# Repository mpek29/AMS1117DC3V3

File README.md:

# AMS1117DC3V3

## 🚀 Overview

An open-source reverse-engineered version of the AMS1117 3.3V DC-DC buck converter module, based on the original component available [here](https://fr.aliexpress.com/item/1005006783027108.html).  
This project aims to provide insights into DC-DC voltage regulation and offer a customizable alternative for power management in embedded systems.

## 🎯 Purpose
- 🔍 **Reverse engineering**: Understanding the design and functionality of the AMS1117-based voltage regulator.
- 🛠️ **Skill development**: Enhancing expertise in PCB design and power electronics.
- 🔄 **Future adaptation**: Leveraging this knowledge to develop custom voltage regulation solutions for embedded applications.

## 📝 Features Comparison: Original vs. Reverse-Engineered

| Feature            | Original Module | Reverse-Engineered Version |
|--------------------|----------------|---------------------------|
| 🖥️ PCB Design        | Proprietary     | Open-source & customizable |
| 🔌 Input Voltage    | 4.8V - 15V       | 4.8V - 15V |
| ⚡ Output Voltage   | 3.3V (fixed)     | 3.3V (fixed) |
| 📦 Max Current     | 1500 mA            | 1500 mA |
| 🏷️ Regulator Chip  | AMS1117-3.3      | AMS1117-3.3 |
| 👐 Mechanical Drawing  |  |  |
| 📝 Reverse-Engineered Schematic | N/A |  |
| 📷 Photo             |  |  |

## 🛠️ How to Use
### 📌 Wiring Guide
| Pin  | Description |
|------|-------------|
| VIN  | Input Voltage (4.8V - 15V) |
| GND  | Ground |
| VOUT | Regulated 3.3V Output |

## 🌟 License
This project is open-source. Feel free to use, modify, and contribute! 🚀

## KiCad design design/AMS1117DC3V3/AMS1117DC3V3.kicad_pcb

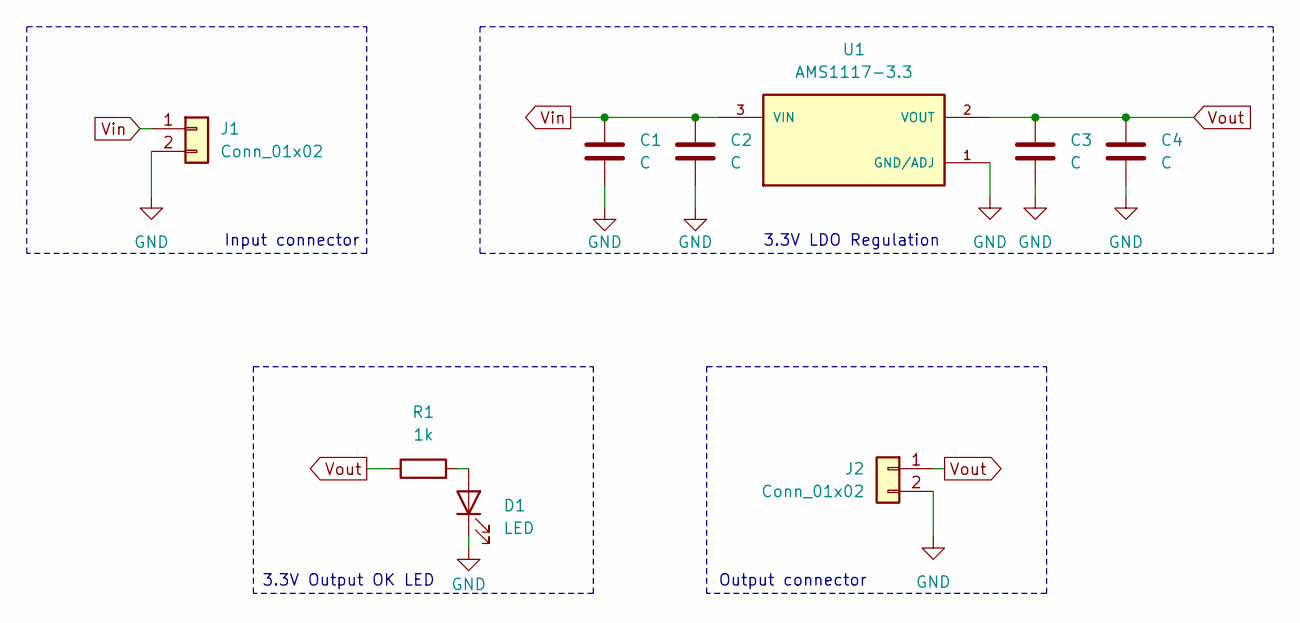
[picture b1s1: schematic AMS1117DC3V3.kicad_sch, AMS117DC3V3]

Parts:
C1, C2, C3, C4: C; C_0603_1608Metric
D1: LED; LED_1206_3216Metric
J1, J2: Conn_01x02; PinHeader_1x02_P2.54mm_Vertical
R1: 1k; R_1206_3216Metric
U1: AMS1117-3.3; SOT229P700X180-4N; PARTREV N/A

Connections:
GND: C1.2, C2.2, C3.2, C4.2, D1.1 (K), J1.2, J2.2, U1.1 (GND/ADJ)
unnamed: D1.2 (A), R1.2
Vin: C1.1, C2.1, J1.1, U1.3 (VIN)
Vout: C3.1, C4.1, J2.1, R1.1, U1.2 (VOUT)

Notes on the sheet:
Input connector
Output connector
3.3V Output OK LED
3.3V LDO Regulation

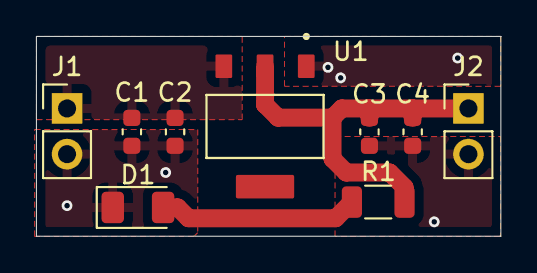
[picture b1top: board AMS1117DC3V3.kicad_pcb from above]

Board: 2 copper layers, 25.8 x 11.1 mm, 9 parts (0 on the bottom side), 4 nets.

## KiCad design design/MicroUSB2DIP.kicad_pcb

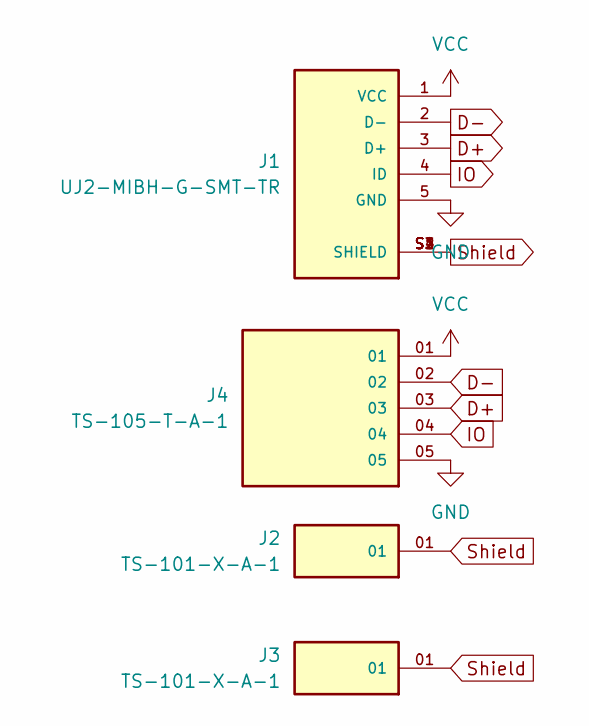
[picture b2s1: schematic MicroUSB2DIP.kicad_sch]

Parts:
J1: UJ2-MIBH-G-SMT-TR; CUI_UJ2-MIBH-G-SMT-TR; PARTREV 1.0
J2, J3: TS-101-X-A-1; SAMTEC_TS-101-X-A-1; PARTREV B
J4: TS-105-T-A-1; SAMTEC_TS-105-T-A-1; PARTREV R

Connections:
D+: J1.3 (D+), J4.03
D-: J1.2 (D-), J4.02
GND: J1.5 (GND), J4.05
IO: J1.4 (ID), J4.04
Shield: J1.S1 (SHIELD), J1.S2 (SHIELD), J1.S3 (SHIELD), J1.S4 (SHIELD), J2.01, J3.01
VCC: J1.1 (VCC), J4.01

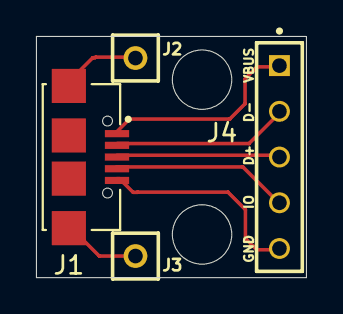
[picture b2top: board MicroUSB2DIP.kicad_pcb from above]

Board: 2 copper layers, 15.0 x 13.4 mm, 4 parts (0 on the bottom side), 6 nets.

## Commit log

2025-02-13 pictures update
2025-02-13 starting of the schematics
2025-02-15 final version
2025-02-15 edit of retro sch
2025-02-15 new pic high
2025-02-19 misc with folder name
